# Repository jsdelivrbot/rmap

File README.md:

/*! \mainpage STIMA Readme
\section introduction Introduction
software to collect weather data contributed by citizens; to make
these data available for weather services and homeland security; to
provide feedback to the data contributors so that they have the tools
to check and improve their data quality

http://rmap.cc

\section howto Howto

\subsection report_eth STIMA Report over Ethernet:

\subsubsection report_eth_1 1)
open sketch arduino/sketchbook/rmap/rmap/rmap.ino

\subsubsection report_eth_2 2)
in rmap-config.h set STIMA_MODULE_TYPE_REPORT_ETH in MODULE_VERSION define

\subsubsection report_eth_3 3)
open arduino/sketchbook/library/RmapConfig/sensors_config.h and set true or false
sensors's define and json's define in order to enable or disable relative sensor driver and library

\subsection report_gsm STIMA Report over GSM:

\subsubsection report_gsm_1 1)
open sketch arduino/sketchbook/rmap/rmap/rmap.ino

\subsubsection report_gsm_2 2)
in rmap-config.h set STIMA_MODULE_TYPE_REPORT_GSM in MODULE_VERSION define

\subsubsection report_gsm_3 3)
open arduino/sketchbook/library/RmapConfig/sensors_config.h and set true or false
sensors's define and json's define in order to enable or disable relative sensor driver and library

\section RmapConfig RmapConfig library

\subsection debug_config debug_config.h:
Enable or disable debug in sketch and library

\subsection ethernet_config ethernet_config.h:
Ethernet configuration's parameters

\subsection gsm_config gsm_config.h:
GSM configuration's parameters

\subsection hardware_config hardware_config.h:
Hardware configuration's parameters

\subsection json_config json_config.h:
JSON configuration's parameters

\subsection lcd_config lcd_config.h:
LCD configuration's parameters

\subsection mqtt_config mqtt_config.h:
MQTT configuration's parameters

\subsection ntp_config ntp_config.h:
NTP configuration's parameters

\subsection sdcard_config sdcard_config.h:
SDCARD configuration's parameters

\subsection sensors_config sensors_config.h:
Enable or disable sensor driver sensors for specific sketch

\section Rmap Rmap library

\subsection debug debug:
Debugging functions for print debug message on serial port or LCD

\subsection eeprom_utility eeprom_utility:
EEPROM utility for write and read eeprom

\subsection i2c_utility i2c_utility:
I2C utility

\subsection registers registers:
General register's define

\subsection registers-th registers-th:
I2C-TH register's define

\subsection registers-rain registers-rain:
I2C-Rain register's define

\subsection rmap_utility rmap_utility:
RMAP useful functions

\subsection sdcard_utility sdcard_utility:
SD-Card useful functions

\subsection stima_module stima_module:
STIMA station's definition

\subsection typedef typedef:
Useful project typedef

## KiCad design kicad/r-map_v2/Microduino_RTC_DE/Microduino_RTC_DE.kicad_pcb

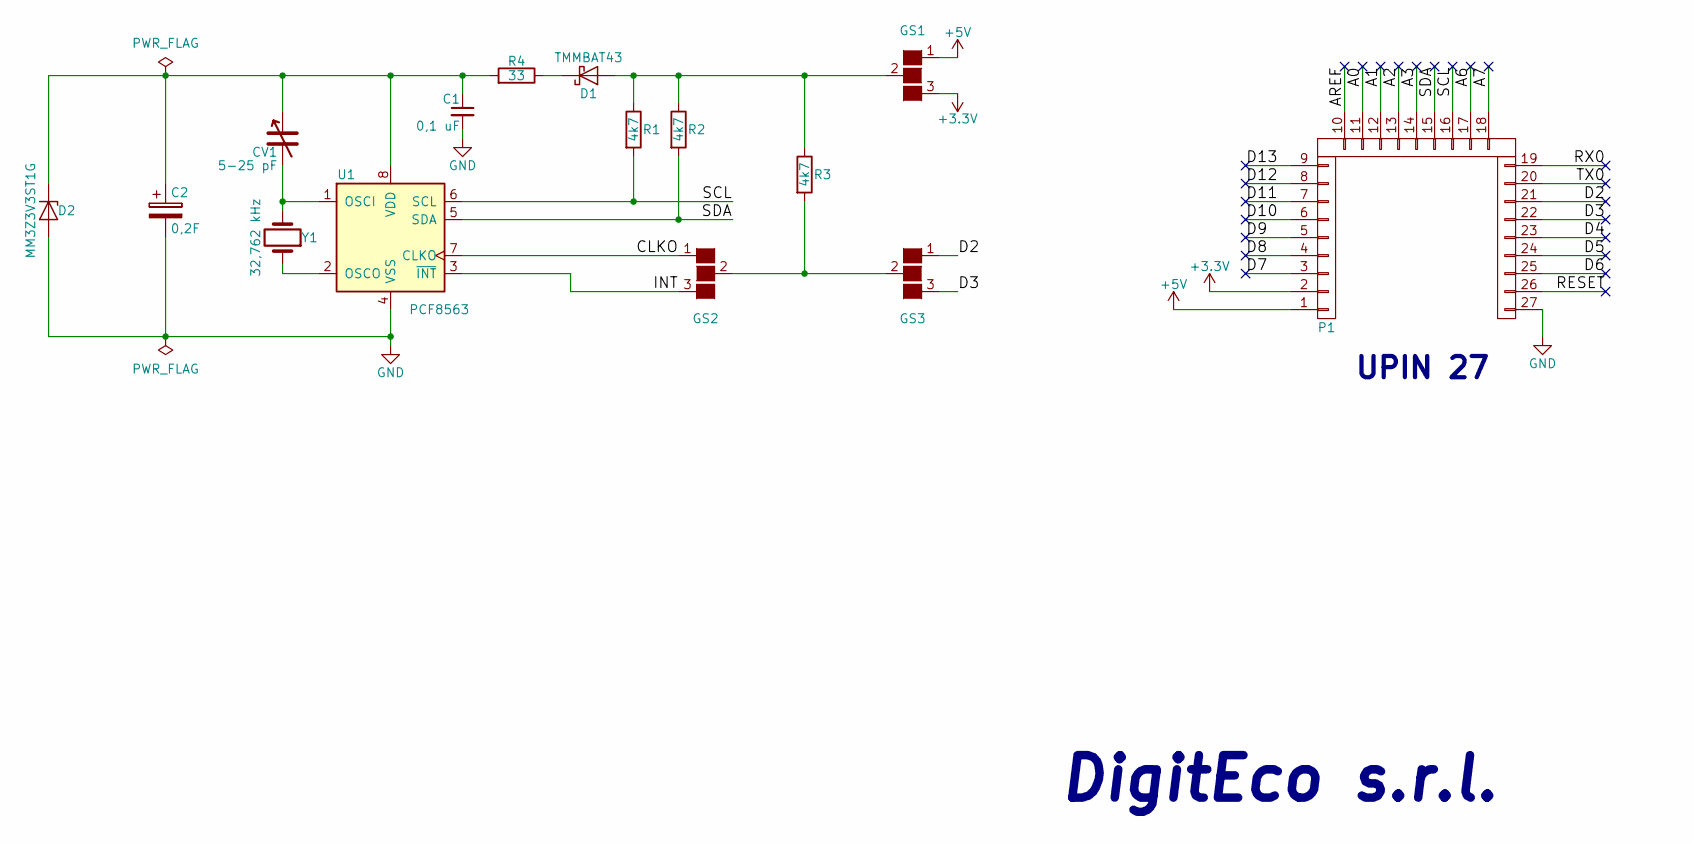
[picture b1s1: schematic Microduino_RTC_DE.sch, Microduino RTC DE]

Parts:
C1: 0,1 uF; C_0805
C2: 0,2F; Supercap
CV1: 5-25 pF; C_1206
D1: TMMBAT43; D_MiniMELF_Standard
D2: MM3Z3V3ST1G; D_SOD-323
GS1, GS2, GS3: GS3
P1: CONN_1x27; Upin_27
R1, R2, R3: 4k7; R_0805
R4: 33; R_0805
U1: PCF8563; SOIC-8_3.9x4.9mm_Pitch1.27mm
Y1: 32,762 kHz; Crystal_SMD_G8-2pin_3.2x1.5mm_HandSoldering

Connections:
+3V3: GS1.3 (G3), P1.2
+5V: GS1.1 (G1), P1.1
/A0: P1.11
/A1: P1.12
/A2: P1.13
/A3: P1.14
/A6: P1.17
/A7: P1.18
/AREF: P1.10
/CLKO: GS2.1 (G1), U1.7 (CLKO); also elsewhere on the board
/D2: GS3.1 (G1), P1.21
/D3: GS3.3 (G3), P1.22
/D4: P1.23
/D5: P1.24
/D6: P1.25
/D7: P1.3
/D8: P1.4
/D9: P1.5
/D10: P1.6
/D11: P1.7
/D12: P1.8
/D13: P1.9
/INT: GS2.3 (G3), U1.3 (~INT~); also elsewhere on the board
/RESET: P1.26
/RX0: P1.19
/SCL: P1.16, R1.2, U1.6 (SCL)
/SDA: P1.15, R2.2, U1.5 (SDA)
/TX0: P1.20
GND: C1.2, C2.2, D2.2 (A), P1.27, U1.4 (VSS)
unnamed: C1.1, C2.1, CV1.1, D2.1 (K), R4.2, U1.8 (VDD)
unnamed: CV1.2, U1.1 (OSCI), Y1.2
unnamed: D1.1 (K), R4.1
unnamed: D1.2 (A), GS1.2 (G2), R1.1, R2.1, R3.1
unnamed 33: GS2.2 (G2), GS3.2 (G2), R3.2; also elsewhere on the board
unnamed: U1.2 (OSCO), Y1.1

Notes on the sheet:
UPIN 27
DigitEco s.r.l.

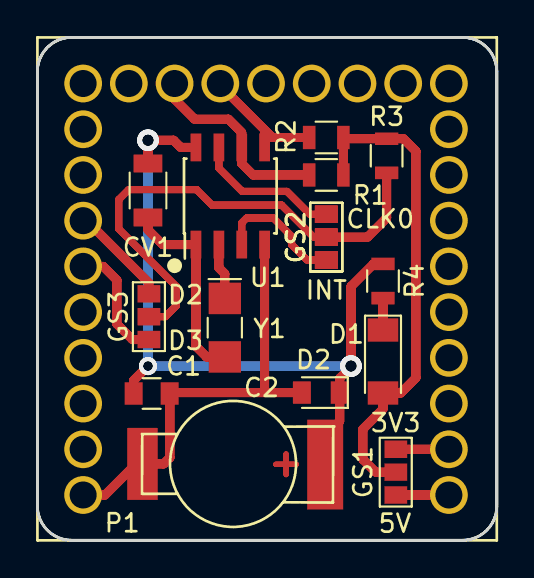
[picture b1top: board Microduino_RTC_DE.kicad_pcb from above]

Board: 2 copper layers, 25.5 x 27.9 mm, 16 parts (1 on the bottom side), 15 nets.

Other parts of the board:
GS2#2: GS3

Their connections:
/CLKO: GS2#2.1; also elsewhere on the board
/INT: GS2#2.3; also elsewhere on the board
unnamed 33: GS2#2.2; also elsewhere on the board

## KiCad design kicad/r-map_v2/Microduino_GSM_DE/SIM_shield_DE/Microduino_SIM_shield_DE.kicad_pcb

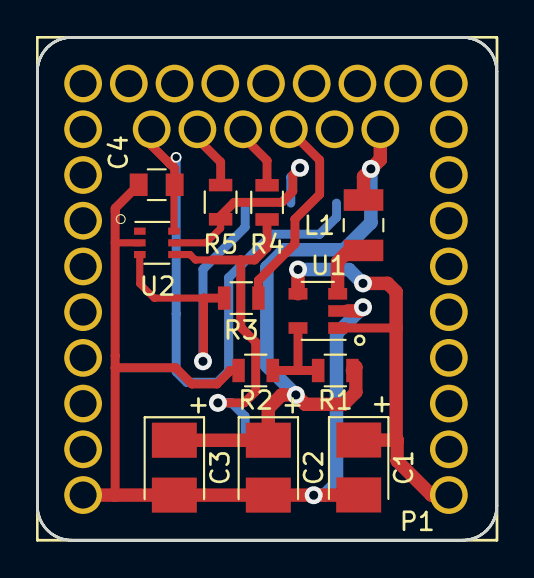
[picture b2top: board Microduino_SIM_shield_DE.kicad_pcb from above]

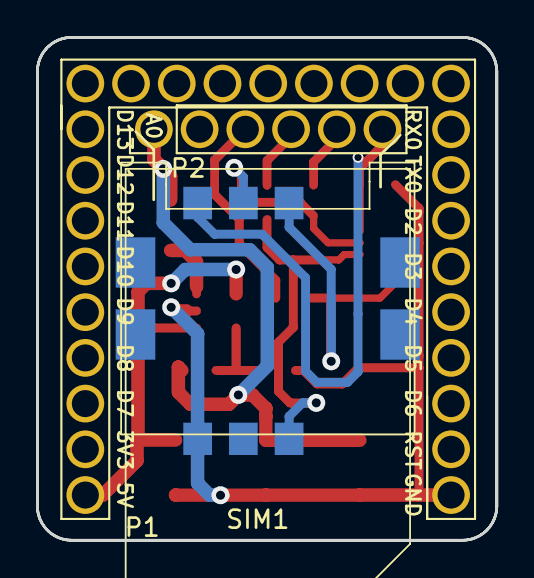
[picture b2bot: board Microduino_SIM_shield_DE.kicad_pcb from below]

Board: 2 copper layers, 25.5 x 27.9 mm, 15 parts (3 on the bottom side), 12 nets.

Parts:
C1, C2, C3: 100uF; CP_Tantalum_Case-B_EIA-3528-21_Reflow
C4: 100nF; C_0805
L1: 2,2 uH; Induttanza_SMD_2520_Wurth
P1: CONN_1x27; Upin_27
P2: CONN_01X06; Pin_Header_Straight_1x06_Pitch2.54mm
R1: 330k; R_0805
R2: 56k; R_0805
R3, R4, R5: 22; R_0805
SIM1: SIM-CARD; mini_sim_card_holder
U1: TLV62569; SOT-23-5
U2: ESDA6V1-5W6; SOT-363_SC-70-6

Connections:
+5V: C1.1, P1.1, U1.1, U1.4
/SIM_CLK: R3.1, SIM1.3, U2.3
/SIM_DATA: R4.1, SIM1.6, U2.4
/SIM_RST: R5.1, SIM1.2, U2.5
/VBAT: C2.1, C3.1, L1.2, P2.1, R1.1
/VSIM: C4.1, P2.6, SIM1.1, U2.6
GND: C1.2, C2.2, C3.2, C4.2, P1.27, R2.2, SIM1.4, U1.2, U2.2
unnamed: L1.1, U1.3
unnamed: P2.3, R3.2
unnamed: P2.4, R4.2
unnamed: P2.5, R5.2
unnamed: R1.2, R2.1, U1.5

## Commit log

2017-09-26 fix tipping bucket debounce
2017-09-26 removed wakeup from wdt and set wake up from timer1
2017-09-26 rename HYT271 to HYT2X1
2017-09-26 added lcd_config.h for configuring i2c-lcd
2017-09-26 modified PCF8563 adding some functions
2017-09-26 addedd support for lcd debug and timer1 sleep
2017-09-26 parameter tuning
2017-09-26 bugfixes
2017-09-26 modified dhcp timeout
2017-09-26 removed hyt271 library
2017-09-26 new kicad hardware project
2017-10-11 rmap bugfix and documentation
2017-10-11 i2c-rain bugfix and documentation
2017-10-11 i2c-th bugfix and documentation
2017-10-11 Modified I2C Library for LCD
2017-10-11 smallfix for Wire
2017-10-11 deleted old I2C Library for LCD
2017-10-11 add small doc to HYT2X1 library
2017-10-11 add client flush
2017-10-11 first doc addedd
2017-10-11 bugfix
2017-10-11 bugfix and first doc added
2017-10-12 update kicad project
2017-10-27 added doc for HYT2X1 library
2017-10-27 added doc for NTP library
2017-10-27 little mod on Rmap library
2017-10-27 added Digiteco Power sensors
2017-10-27 little mod on RmapConfig library
2017-10-27 removed old functions
2017-10-27 bugfix and doc update
2017-10-30 add DigitecoPower library
2017-10-30 update doc
2017-10-30 update avr platform
2017-10-30 add main doc
2017-11-09 removed old lib
2017-11-09 upload to last microduino avr lib
2017-11-09 revert boards.txt to original state
2017-11-13 documentation update
2017-11-14 update documentation
2017-11-15 add dynamic mqtt client generation
2017-12-07 add ArduinoJson
2017-12-07 small fix and example added
2017-12-07 correct timezone to GMT zone
2017-12-07 small fix and improvements
2017-12-07 small fix and debug with progmem added
2017-12-07 small fix
2017-12-07 fix configuration by sensors_config
2017-12-07 bugfix and general improvementds
2017-12-07 modified sensor_config for new i2c-rain and i2c-th
2017-12-07 kicad schemas update
2017-12-11 add support for ADT and HIH sensors in SensorDriver and update examples
2017-12-11 doc update
2017-12-11 add DW1 sensor in SensorDriver and test update
2017-12-19 bugfix and general improvements
2018-06-14 fix init function
2018-06-14 change default apn
2018-06-14 add support for maint topic
2018-06-14 general improvement for testing sensor driver
2018-06-14 remove bound level for sensors measurement, addedd support for wind and general bugfix
2018-06-14 general bugfgix
2018-06-14 add windsonic to sensor driver
2018-06-14 general bugfix
2018-06-14 add support for maint topic and switch rmap version into 2 variable
2018-06-14 add digitecoboot
2018-07-09 fix memset init (not an error)
2018-07-09 init sensor error display on lcd
2018-07-09 fix data processing in case of error
2018-07-09 change minor version to 2
2018-10-23 question on power save
2018-11-07 Created a copy of python2.7 code
2018-11-07 startin with migration to python3 with 2to3 and other minor
2018-11-07 Serialize Trange and Level classes #277
2018-11-07 new gitignore
2018-11-07 porting to django 2
2018-11-07 generic python3 interpreter
2018-11-07 migrate to django 2
2018-11-07 buildozer new toolchain
2018-11-07 working on composereport python3
2018-11-07 little bug in profile
2018-11-07 porting to python3
2018-11-07 working on python 3 manage.py setted for python3 progiling ported to python3 migration file
2018-11-07 version 8.0 working on python3
2018-11-07 ttn2dballe bug for python3
2018-11-07 migration to python3 terminated. Ready to check
2018-11-07 replicate bug
2018-11-07 ignore buildozer and static dir
2018-11-07 try to build apk with crystax-ndk
2018-11-07 updated mapview to mainstream
2018-11-07 porting to kivy-1.10.1
2018-11-07 working on python3 porting
2018-11-07 syntax error
2018-11-07 delay in serial transport required by stima v3
2018-11-07 MergeDB use a string value to sort the records #276
